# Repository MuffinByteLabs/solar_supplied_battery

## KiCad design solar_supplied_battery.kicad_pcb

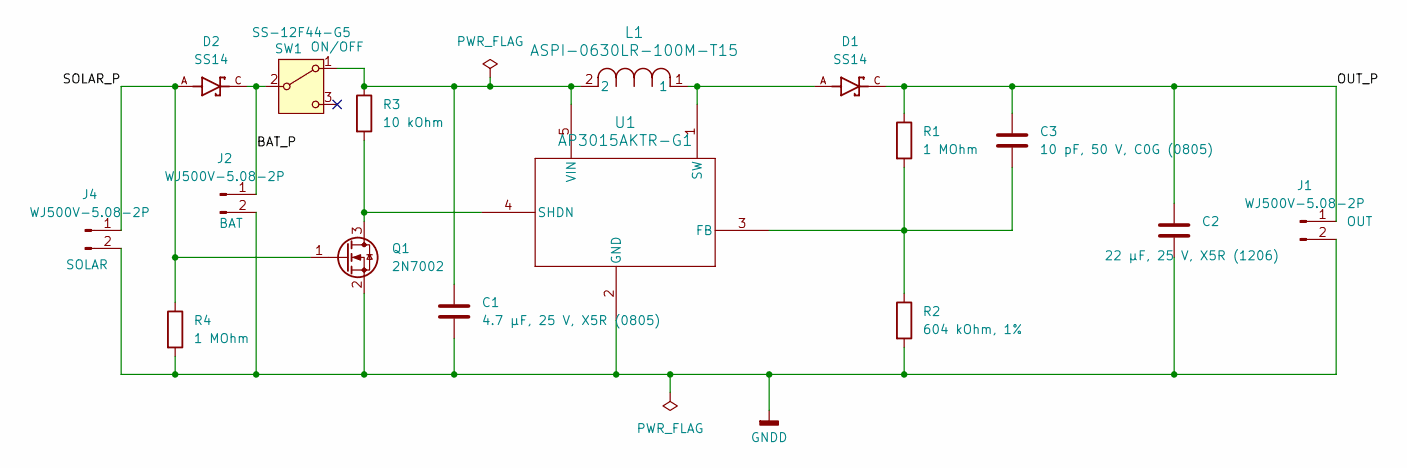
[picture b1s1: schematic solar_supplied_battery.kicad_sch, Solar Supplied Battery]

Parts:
C1: 4.7 µF, 25 V, X5R (0805); C_0805_2012Metric; JLCPCB Part C1779
C2: 22 µF, 25 V, X5R (1206); C_1206_3216Metric; JLCPCB Part C12891
C3: 10 pF, 50 V, C0G (0805); C_0805_2012Metric; JLCPCB Part C157608
D1, D2: SS14; PARTREV O2102; JLCPCB Part C2480
J1, J2, J4: WJ500V-5.08-2P; TerminalBlock_Phoenix_MKDS-3-2-5.08_1x02_P5.08mm_Horizontal; JLCPCB Part C8465
L1: ASPI-0630LR-100M-T15; IND_ASPI-0630LR-100M-T15; JLCPCB Part C1334133
Q1: 2N7002; SOT-23; JLCPCB Part C8545
R1, R4: 1 MOhm; R_0805_2012Metric; JLCPCB Part C17514
R2: 604 kOhm, 1%; R_0805_2012Metric; JLCPCB Part C17776
R3: 10 kOhm; R_0805_2012Metric; JLCPCB Part C17414
SW1: SS-12F44-G5; SW-TH_SS-12F44-G5; JLCPCB Part C136718
U1: AP3015AKTR-G1; JLCPCB Part C154879

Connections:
/BAT_P: D2.C, J2.1, SW1.2 (B)
/OUT_P: C2.1, C3.1, D1.C, J1.1, R1.1
/SOLAR_P: D2.A, J4.1, Q1.1 (G), R4.1
GNDD: C1.2, C2.2, J1.2, J2.2, J4.2, Q1.2 (S), R2.2, R4.2, U1.2 (GND)
unnamed: Q1.3 (D), R3.2, U1.4 (SHDN)
unnamed: C1.1, L1.2, R3.1, SW1.1 (A), U1.5 (VIN)
unnamed: C3.2, R1.2, R2.1, U1.3 (FB)
unnamed: D1.A, L1.1, U1.1 (SW)

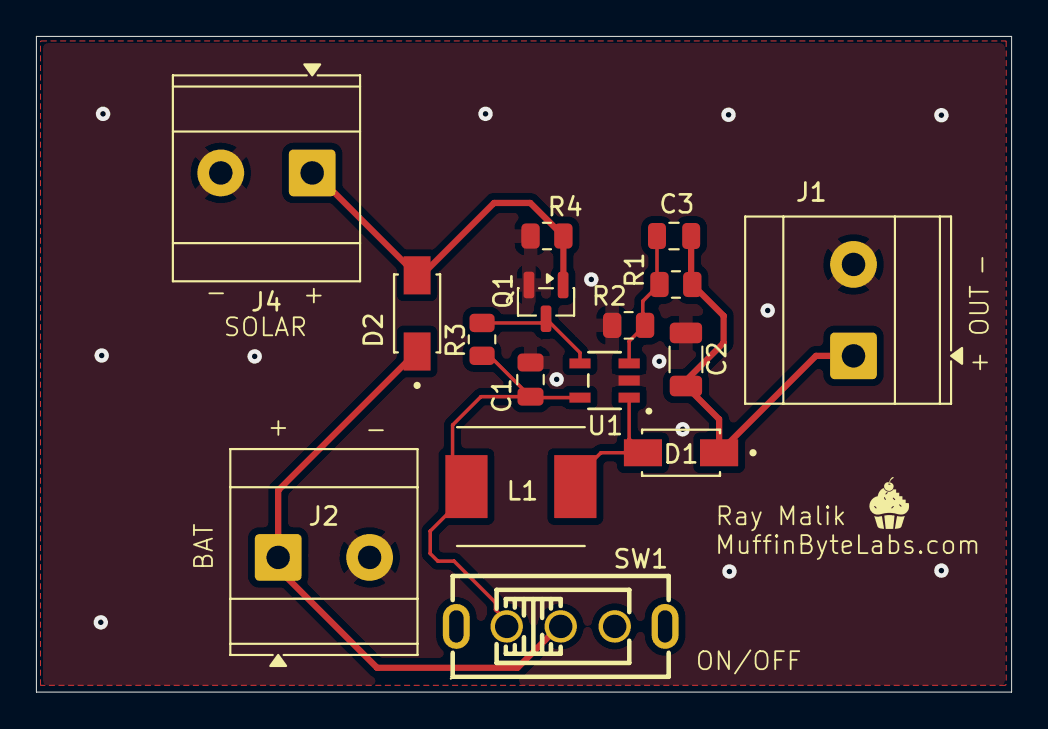
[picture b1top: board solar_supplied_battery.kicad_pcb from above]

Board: 2 copper layers, 54.2 x 36.4 mm, 16 parts (0 on the bottom side), 8 nets.

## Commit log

2026-05-25 Initial commit: solar supplied battery KiCad project
2026-05-26 finished schema, just starting the pcb layout
2026-05-29 starting routes
2026-05-30 reorganized folders and importing footprints
2026-05-31 finished routing, now just have to make vias for the ground fills
2026-06-03 finalized the physical components, just have to do gerber and bom
2026-06-07 finished layout and bom
